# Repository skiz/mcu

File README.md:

Motor Control Unit
==================

Overview
--------
This hardware project is based on several existing Arduino boards,
and shields, combining them along with some additional hardware to
provide clean bipolar 10vdc control of up to 3 industrial motor
control units for use with the [SMC3](https://github.com/SimulatorMotorController) 
motion platform software available on Github.

The SMC3 software suite is specifically designed to interact with 
[SimTools](https://www.xsimulator.net/) which generates motion queues
from existing simulator integrations running on Windows.

The schematic, PCB, and related files have been exclusively created in [KiCad](kicad-pcb.org/).

Structure
---------
There are several directories which contain various references for the project;

* board      - The KiCad project itself: PCB, Schematic, etc.
* bom        - Bill of Materials required to assemble the complete PCB.
* datasheets - All datasheets related to the componented used in the design.
* libraries  - Libraries specific to this design (PCB footprints & Symbols).
* models     - 3d models used for rendering the board
* renders    - 2D/3D renderings of the board, and misc images

Parent Hardware
---------------
As this is a culmination of existing OSS hardware, it's only appropriate to
list the "donors" here.  The hardware here basically consists of stripped
down Adafruit Motor Shield V2, and some additional DAC
conversions and voltage regulation for +/-10v analog DC output.

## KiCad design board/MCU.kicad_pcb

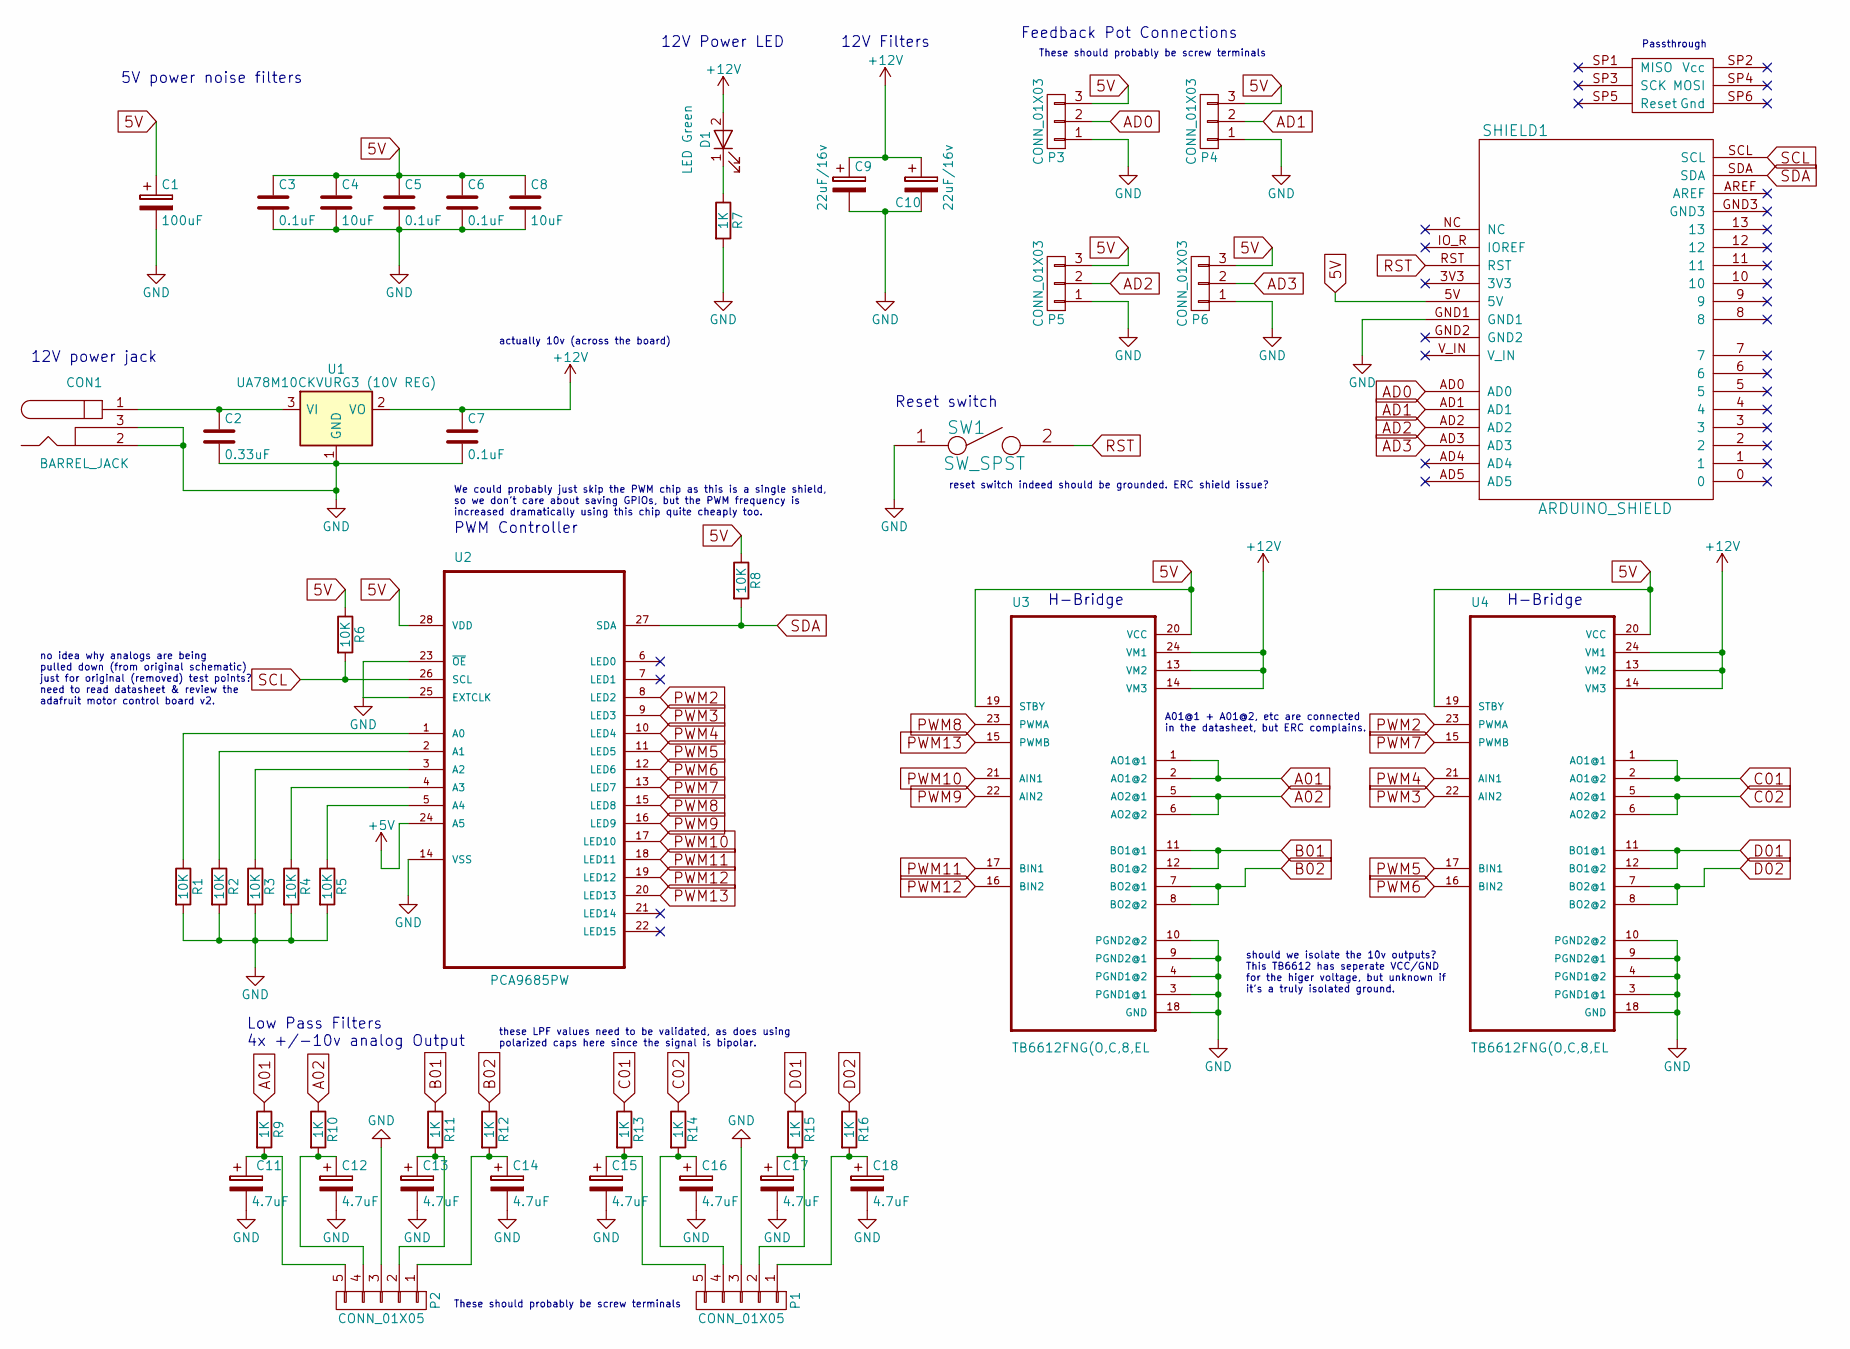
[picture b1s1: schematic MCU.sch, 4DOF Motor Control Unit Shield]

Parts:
C1: 100uF; SMD-1206_Pol
C2: 0.33uF; C_0603
C3, C5, C6, C7: 0.1uF; C_0603
C4, C8: 10uF; C_0603
C9, C10: 22uF/16v; c_elec_4x5.8
C11, C12, C13, C14, C15, C16, C17, C18: 4.7uF; c_elec_3x5.3
CON1: BARREL_JACK; JACK_ALIM
D1: LED Green; LED_1206
P1, P2: CONN_01X05; Pin_Header_Straight_1x05
P3, P4, P5, P6: CONN_01X03; Pin_Header_Straight_1x03
R1, R2, R3, R4, R5, R6, R8: 10K; R_0603
R7, R9, R10, R11, R12, R13, R14, R15, R16: 1K; R_0603
SHIELD1: ARDUINO_SHIELD
SW1: SW_SPST; SW_SPST_B3SL-1002P
U1: UA78M10CKVURG3 (10V REG); TO-252-3
U2: PCA9685PW; SOP65P640X110-28N
U3, U4: TB6612FNG(O,C,8,EL; SOP65P760X160-24N

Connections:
5V: C1.1, C3.1, C4.1, C5.1, C6.1, C8.1, P3.3, P4.3, P5.3, P6.3, R6.1, R8.1, SHIELD1.5V, U2.28 (VDD), U3.19 (STBY), U3.20 (VCC), U4.19 (STBY), U4.20 (VCC)
+12V: C7.1, C9.1, C10.1, D1.2 (A), U1.2 (VO), U3.13 (VM2), U3.14 (VM3), U3.24 (VM1), U4.13 (VM2), U4.14 (VM3), U4.24 (VM1)
A01: R9.1, U3.1 (AO1@1), U3.2 (AO1@2)
A02: R10.1, U3.5 (AO2@1), U3.6 (AO2@2)
AD0: P3.2, SHIELD1.AD0
AD1: P4.2, SHIELD1.AD1
AD2: P5.2, SHIELD1.AD2
AD3: P6.2, SHIELD1.AD3
B01: R11.1, U3.11 (BO1@1), U3.12 (BO1@2)
B02: R12.1, U3.7 (BO2@1), U3.8 (BO2@2)
C01: R13.1, U4.1 (AO1@1), U4.2 (AO1@2)
C02: R14.1, U4.5 (AO2@1), U4.6 (AO2@2)
D01: R15.1, U4.11 (BO1@1), U4.12 (BO1@2)
D02: R16.1, U4.7 (BO2@1), U4.8 (BO2@2)
GND: C1.2, C2.2, C3.2, C4.2, C5.2, C6.2, C7.2, C8.2, C9.2, C10.2, C11.2, C12.2, C13.2, C14.2, C15.2, C16.2, C17.2, C18.2, CON1.2, CON1.3, P1.3, P2.3, P3.1, P4.1, P5.1, P6.1, R1.2, R2.2, R3.2, R4.2, R5.2, R7.2, SHIELD1.GND1, SW1.1, U1.1 (GND), U2.14 (VSS), U2.23 (~OE), U2.25 (EXTCLK), U3.3 (PGND1@1), U3.4 (PGND1@2), U3.9 (PGND2@1), U3.10 (PGND2@2), U3.18 (GND), U4.3 (PGND1@1), U4.4 (PGND1@2), U4.9 (PGND2@1), U4.10 (PGND2@2), U4.18 (GND); also elsewhere on the board
unnamed 15: C2.1, CON1.1, U1.3 (VI); also elsewhere on the board
unnamed: C11.1, P2.5, R9.2
unnamed: C12.1, P2.4, R10.2
unnamed: C13.1, P2.2, R11.2
unnamed: C14.1, P2.1, R12.2
unnamed: C15.1, P1.5, R13.2
unnamed: C16.1, P1.4, R14.2
unnamed: C17.1, P1.2, R15.2
unnamed: C18.1, P1.1, R16.2
unnamed: D1.1 (K), R7.1
unnamed: R1.1, U2.1 (A0)
unnamed: R2.1, U2.2 (A1)
unnamed: R3.1, U2.3 (A2)
unnamed: R4.1, U2.4 (A3)
unnamed: R5.1, U2.5 (A4)
PWM2: U2.8 (LED2), U4.23 (PWMA)
PWM3: U2.9 (LED3), U4.22 (AIN2)
PWM4: U2.10 (LED4), U4.21 (AIN1)
PWM5: U2.11 (LED5), U4.17 (BIN1)
PWM6: U2.12 (LED6), U4.16 (BIN2)
PWM7: U2.13 (LED7), U4.15 (PWMB)
PWM8: U2.15 (LED8), U3.23 (PWMA)
PWM9: U2.16 (LED9), U3.22 (AIN2)
PWM10: U2.17 (LED10), U3.21 (AIN1)
PWM11: U2.18 (LED11), U3.17 (BIN1)
PWM12: U2.19 (LED12), U3.16 (BIN2)
PWM13: U2.20 (LED13), U3.15 (PWMB)
RST: SHIELD1.RST, SW1.2
SCL: R6.2, SHIELD1.SCL, U2.26 (SCL)
SDA: R8.2, SHIELD1.SDA, U2.27 (SDA)

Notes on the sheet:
Reset switch
12V Power LED
5V power noise filters
PWM Controller
H-Bridge
12V power jack
Feedback Pot Connections
Low Pass Filters 4x +/-10v analog Output
A01@1 + A01@2, etc are connected in the datasheet, but ERC complains.
12V Filters
no idea why analogs are being pulled down (from original schematic) just for original (removed) test points? need to read datasheet & review the adafruit motor control board v2.
should we isolate the 10v outputs? This TB6612 has seperate VCC/GND for the higer voltage, but unknown if it's a truly isolated ground.
actually 10v (across the board)
these LPF values need to be validated, as does using polarized caps here since the signal is bipolar.
We could probably just skip the PWM chip as this is a single shield, so we don't care about saving GPIOs, but the PWM frequency is increased dramatically using this chip quite cheaply too.
These should probably be screw terminals
reset switch indeed should be grounded. ERC shield issue?
Passthrough

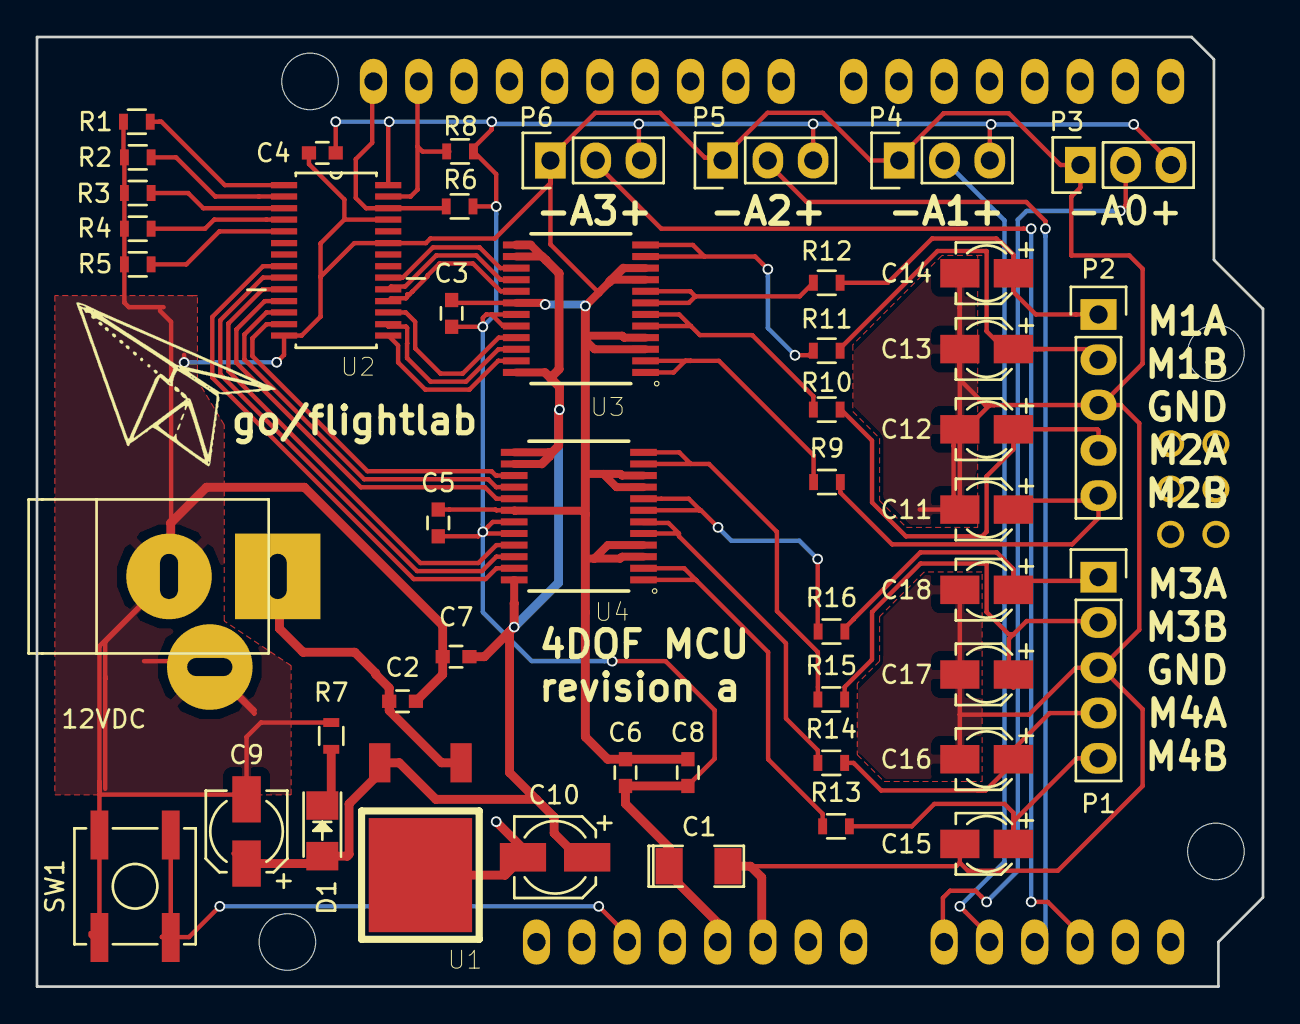
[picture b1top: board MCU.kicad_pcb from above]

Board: 2 copper layers, 68.8 x 53.2 mm, 48 parts (0 on the bottom side), 45 nets.

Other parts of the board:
12VDC: BARREL_JACK; JACK_ALIM

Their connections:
GND: 12VDC.2, 12VDC.3; also elsewhere on the board
unnamed 15: 12VDC.1; also elsewhere on the board

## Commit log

2017-06-09 MCU revision a
2017-06-09 Update to latest render
2017-06-22 Rev B
